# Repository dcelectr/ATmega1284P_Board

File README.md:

# ATmega1284P_Board
ATmega1284P board design is based on the [MightyCore](https://github.com/MCUdude/MightyCore).

The board features fairly easy to hand solder components, such as 0805 resistors, capacitors and LEDs, and it is breadboard friendly (100 mil spacing pin headers) with an orderly pin arrangement [(0 to 23, and A0 to A7)](https://camo.githubusercontent.com/318afd7cb36e720ea851fb34409d54c36701d0300eade1ba0faea744f00fc5db/68747470733a2f2f692e696d6775722e636f6d2f4b3334785a62342e6a7067) of the TQFP-44 package. 

The programming connector is a standard FTDI USB-UART adapter pin-out. The solder jumper (JP1) is closed by default. The board can be powered from the breadboard pin headers or the FTDI programming header. Using an FTDI TTL-232RG-VIP USB-UART adapter, the TTL voltage (Vttl) would be the same as the Vcc.

The Bill of Materials is also included (see file ATmega1284P.csv).

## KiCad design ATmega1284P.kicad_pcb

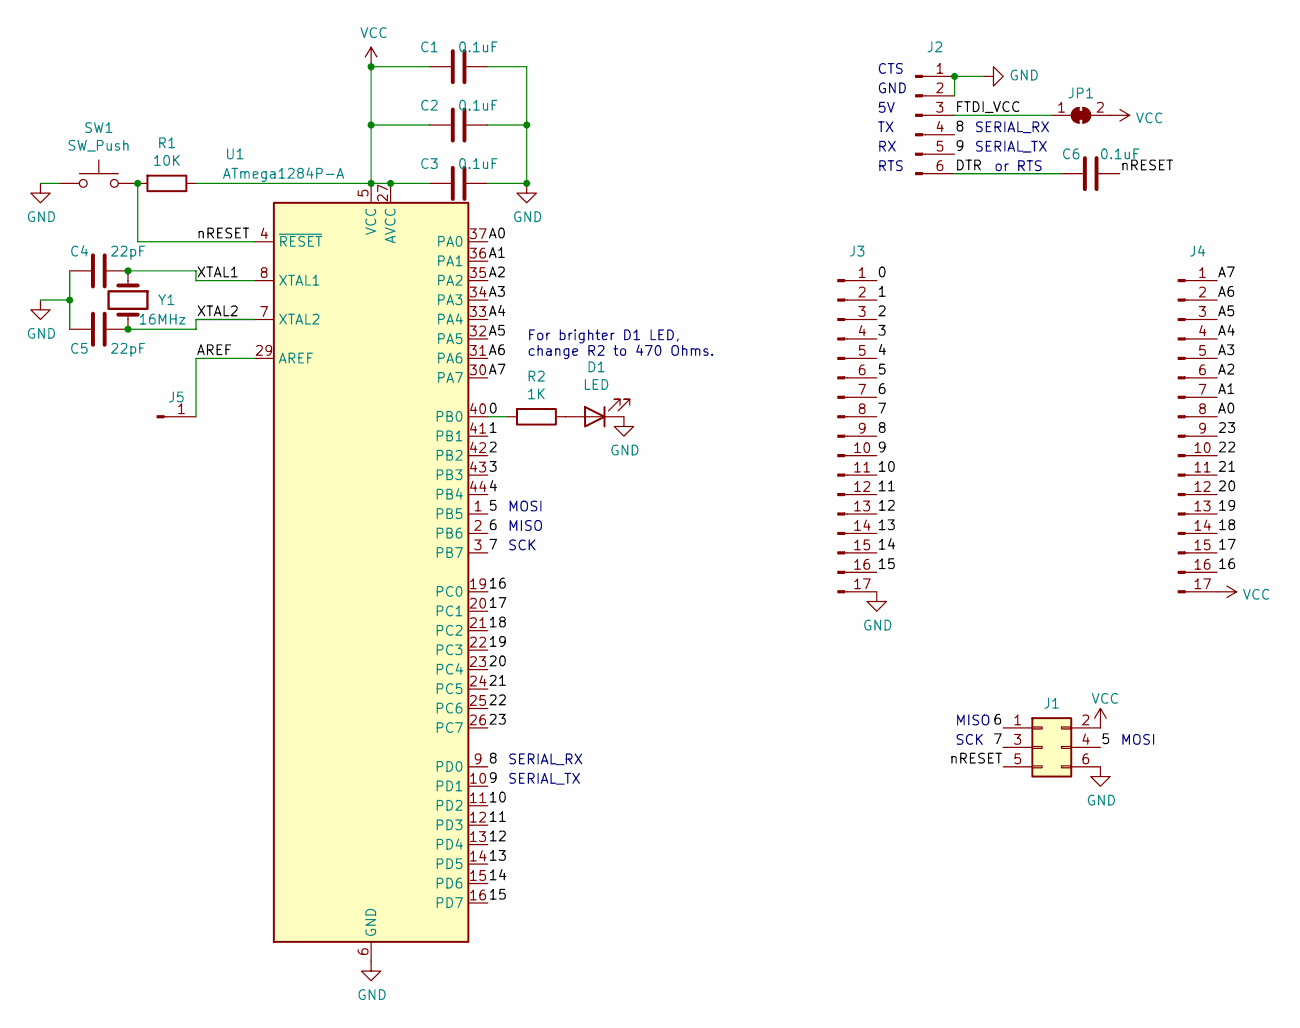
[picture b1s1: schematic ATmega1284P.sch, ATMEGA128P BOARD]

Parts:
C1, C2, C3, C6: 0.1uF; C_0805_2012Metric_Pad1.18x1.45mm_HandSolder
C4, C5: 22pF; C_0603_1608Metric_Pad1.08x0.95mm_HandSolder
D1: LED; LED_0805_2012Metric_Pad1.15x1.40mm_HandSolder
J1: Conn_02x03_Odd_Even; PinHeader_2x03_P2.54mm_Vertical
J2: Conn_01x06_Male; PinHeader_1x06_P2.54mm_Vertical
J3, J4: Conn_01x17_Male; PinHeader_1x17_P2.54mm_Vertical
J5: Conn_01x01_Male; PinHeader_1x01_P2.54mm_Vertical
JP1: SolderJumper_2_Bridged; SolderJumper-2_P1.3mm_Bridged_RoundedPad1.0x1.5mm
R1: 10K; R_0805_2012Metric_Pad1.20x1.40mm_HandSolder
R2: 1K; R_0805_2012Metric_Pad1.20x1.40mm_HandSolder
SW1: SW_Push; SW_SPST_B3U-1000P
U1: ATmega1284P-A; TQFP-44_10x10mm_P0.8mm
Y1: 16MHz; Crystal_SMD_5032-2Pin_5.0x3.2mm

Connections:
/0: J3.1, R2.2, U1.40 (PB0)
/1: J3.2, U1.41 (PB1)
/2: J3.3, U1.42 (PB2)
/3: J3.4, U1.43 (PB3)
/4: J3.5, U1.44 (PB4)
/5: J1.4, J3.6, U1.1 (PB5)
/6: J1.1, J3.7, U1.2 (PB6)
/7: J1.3, J3.8, U1.3 (PB7)
/8: J2.4, J3.9, U1.9 (PD0)
/9: J2.5, J3.10, U1.10 (PD1)
/10: J3.11, U1.11 (PD2)
/11: J3.12, U1.12 (PD3)
/12: J3.13, U1.13 (PD4)
/13: J3.14, U1.14 (PD5)
/14: J3.15, U1.15 (PD6)
/15: J3.16, U1.16 (PD7)
/16: J4.16, U1.19 (PC0)
/17: J4.15, U1.20 (PC1)
/18: J4.14, U1.21 (PC2)
/19: J4.13, U1.22 (PC3)
/20: J4.12, U1.23 (PC4)
/21: J4.11, U1.24 (PC5)
/22: J4.10, U1.25 (PC6)
/23: J4.9, U1.26 (PC7)
/A0: J4.8, U1.37 (PA0)
/A1: J4.7, U1.36 (PA1)
/A2: J4.6, U1.35 (PA2)
/A3: J4.5, U1.34 (PA3)
/A4: J4.4, U1.33 (PA4)
/A5: J4.3, U1.32 (PA5)
/A6: J4.2, U1.31 (PA6)
/A7: J4.1, U1.30 (PA7)
/AREF: J5.1, U1.29 (AREF)
/DTR: C6.2, J2.6
/FTDI_VCC: J2.3, JP1.1 (A)
/XTAL1: C4.1, U1.8 (XTAL1), Y1.1
/XTAL2: C5.1, U1.7 (XTAL2), Y1.2
/nRESET: C6.1, J1.5, R1.2, SW1.2, U1.4 (~RESET)
GND: C1.1, C2.1, C3.1, C4.2, C5.2, D1.1 (K), J1.6, J2.1, J2.2, J3.17, SW1.1, U1.6 (GND), U1.18 (GND), U1.28 (GND), U1.39 (GND)
unnamed: D1.2 (A), R2.1
VCC: C1.2, C2.2, C3.2, J1.2, J4.17, JP1.2 (B), R1.1, U1.5 (VCC), U1.17 (VCC), U1.27 (AVCC), U1.38 (VCC)

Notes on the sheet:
SERIAL_RX
SERIAL_TX
MOSI
MISO
SCK
or RTS
CTS
GND
RTS
For brighter D1 LED, change R2 to 470 Ohms.

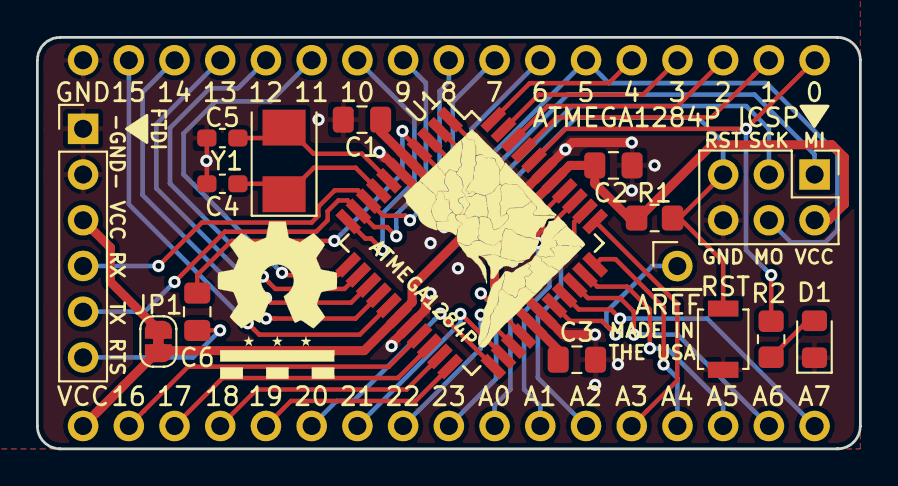
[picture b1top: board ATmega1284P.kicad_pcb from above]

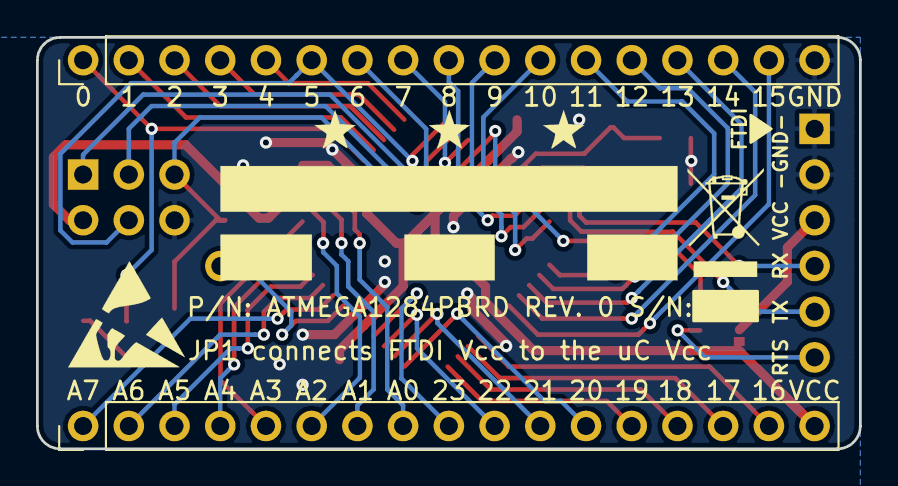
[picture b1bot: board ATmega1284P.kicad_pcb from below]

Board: 2 copper layers, 45.7 x 22.9 mm, 18 parts (2 on the bottom side), 41 nets.

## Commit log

2020-11-18 KiCad Files
2020-11-18 KiCad Files
    Added PDF schematic
2020-11-18 KiCad Files
    Aligned AREF pin to be 0.1" offset from the ICSP
2020-12-15 Added silkscreen under the ATmega1284P chip
    Added the District of Columbia map shape (silkscreen) under the ATmega1284P chip.
